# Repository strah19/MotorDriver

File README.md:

# Motor Driver

This was a simple PCB project to control two DC motors. It includes the schematics and all the needed gerber files for the PCB.

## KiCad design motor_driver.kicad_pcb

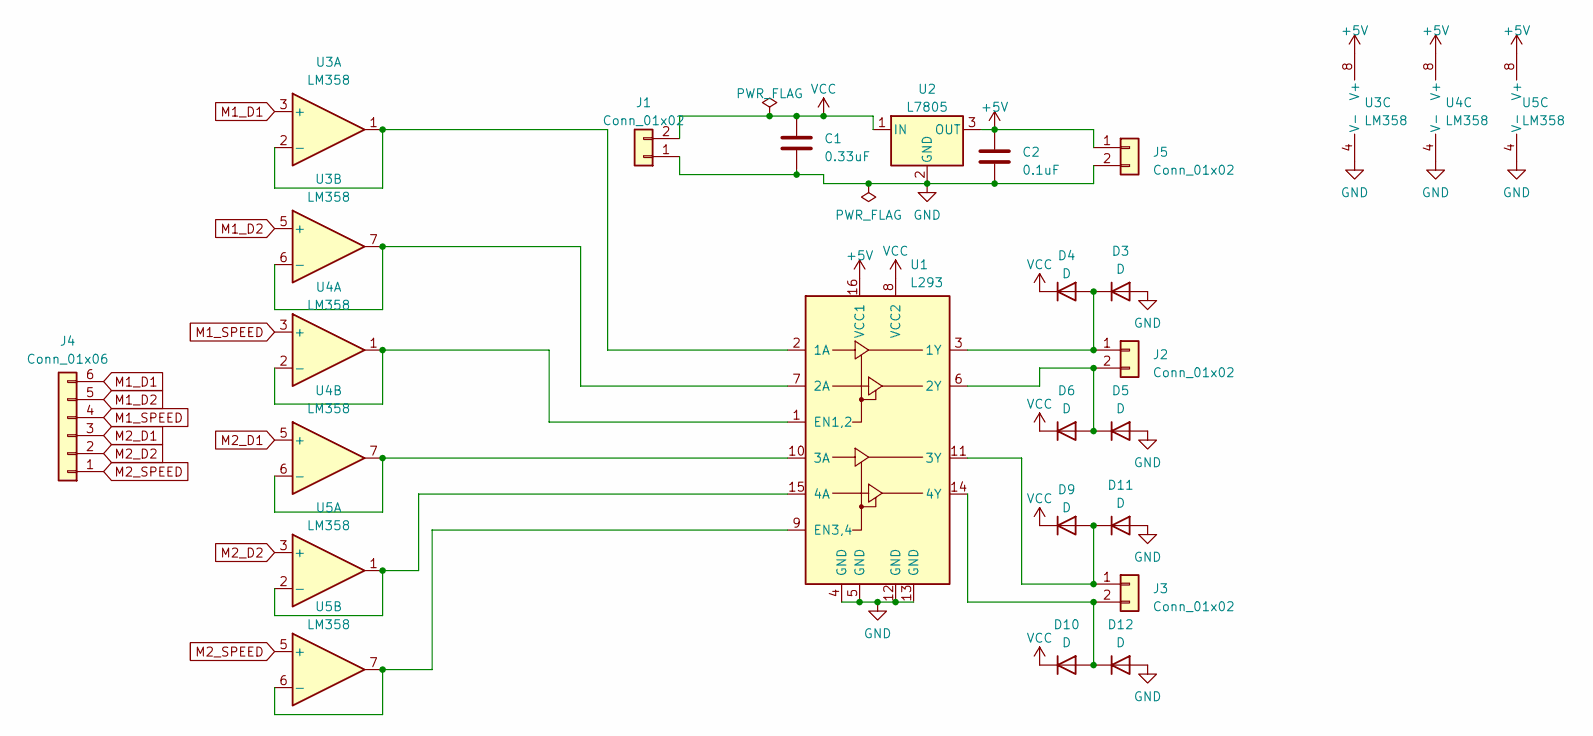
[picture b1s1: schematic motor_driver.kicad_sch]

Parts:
C1: 0.33uF; C_Disc_D5.1mm_W3.2mm_P5.00mm
C2: 0.1uF; C_Disc_D5.1mm_W3.2mm_P5.00mm
D3, D4, D5, D6, D9, D10, D11, D12: D; D_A-405_P7.62mm_Horizontal
J1, J2, J3, J5: Conn_01x02; TerminalBlock_bornier-2_P5.08mm
J4: Conn_01x06; PinSocket_1x06_P2.54mm_Vertical
U1: L293; DIP-16_W7.62mm_Socket
U2: L7805; TO-220-3_Vertical
U3, U4, U5: LM358; DIP-8_W7.62mm_Socket

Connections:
+5V: C2.1, J5.1, U1.16 (VCC1), U2.3 (OUT), U3.8 (V+), U4.8 (V+), U5.8 (V+)
GND: C1.2, C2.2, D3.2 (A), D5.2 (A), D11.2 (A), D12.2 (A), J1.1, J5.2, U1.4 (GND), U1.5 (GND), U1.12 (GND), U1.13 (GND), U2.2 (GND), U3.4 (V-), U4.4 (V-), U5.4 (V-)
M1_D1: J4.6, U3.3 (+)
M1_D2: J4.5, U3.5 (+)
M1_SPEED: J4.4, U4.3 (+)
M2_D1: J4.3, U4.5 (+)
M2_D2: J4.2, U5.3 (+)
M2_SPEED: J4.1, U5.5 (+)
unnamed: D3.1 (K), D4.2 (A), J2.1, U1.3 (1Y)
unnamed: D5.1 (K), D6.2 (A), J2.2, U1.6 (2Y)
unnamed: D10.2 (A), D12.1 (K), J3.2, U1.14 (4Y)
unnamed: D9.2 (A), D11.1 (K), J3.1, U1.11 (3Y)
unnamed: U1.2 (1A), U3.1, U3.2 (-)
unnamed: U1.7 (2A), U3.6 (-), U3.7
unnamed: U1.10 (3A), U4.6 (-), U4.7
unnamed: U1.15 (4A), U5.1, U5.2 (-)
unnamed: U1.1 (EN1,2), U4.1, U4.2 (-)
unnamed: U1.9 (EN3,4), U5.6 (-), U5.7
VCC: C1.1, D4.1 (K), D6.1 (K), D9.1 (K), D10.1 (K), J1.2, U1.8 (VCC2), U2.1 (IN)

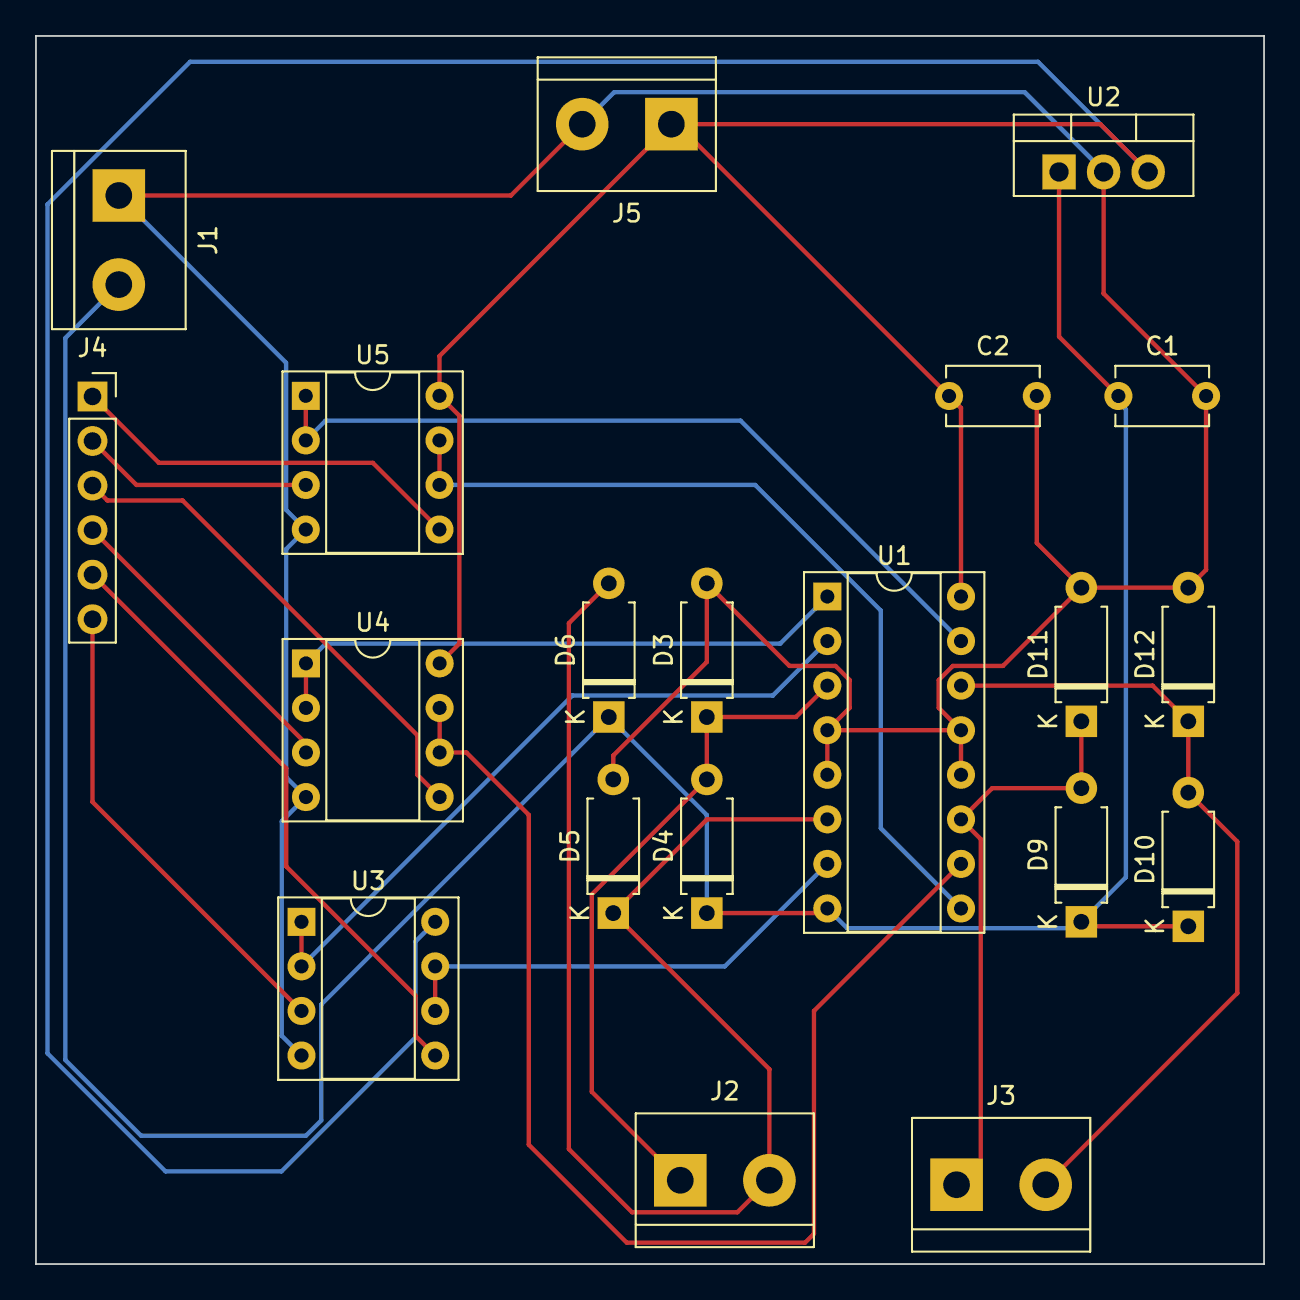
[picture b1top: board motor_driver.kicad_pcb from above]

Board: 2 copper layers, 70.0 x 70.0 mm, 20 parts (0 on the bottom side), 19 nets.

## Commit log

2024-06-24 misspelled file.
